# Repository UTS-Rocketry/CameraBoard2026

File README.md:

# CameraBoard – UTS Rocketry Avionics
High-reliability camera control and downlink board built around the **STM32F405RGT6**, designed for UTS Rocketry’s flight avionics stack.  
The board provides **camera power switching**, **camera UART control**, **video downlink support**, and **CAN-based communication** with the central avionics system.

---

## Project Overview
The CameraBoard is a custom PCB designed to interface action cameras with the UTS Rocketry avionics system.  
It provides:

- **Reliable power delivery** to the camera through a load-switch architecture  
- **UART-based camera control** (start/stop recording, mode switching, etc.)  
- **Video downlink support** (placeholder until RF/video module is finalised)  
- **CAN Bus** connectivity for inter-module communication  
- **Debug UART** and activity LEDs  
- **5V → 3.3V power tree** and full onboard decoupling network  

Built around the **STM32F405RGT6**, chosen for performance, CAN support, and strong STM32 ecosystem compatibility.

---

## Key Features
- **STM32F405RGT6 MCU**
- **Camera Power Switching**
  - Load switch controlled via GPIO  
  - Local decoupling + bulk capacitance
- **Camera Control (UART)**
  - Compatible with RunCam-style UART protocols
- **CAN Bus Interface**
  - TX/RX routed to CAN transceiver  
  - Interfaces with the main flight computer
- **Video Downlink Support**
  - Reserved connector footprint  
  - Pins allocated for future video transmitter module
- **Debug Interface**
  - UART for logging  
  - Status, power, and activity LEDs
- **Power Topology**
  - Headers for 5V buck converters  
  - 3.3V rail for MCU and logic  
  - Full decoupling network following ST guidelines

## Current Project Status
Schematic Finalized

## Contributors
Reed Basangan — Software Lead, UTS Rocketry
UTS Rocketry Avionics Team

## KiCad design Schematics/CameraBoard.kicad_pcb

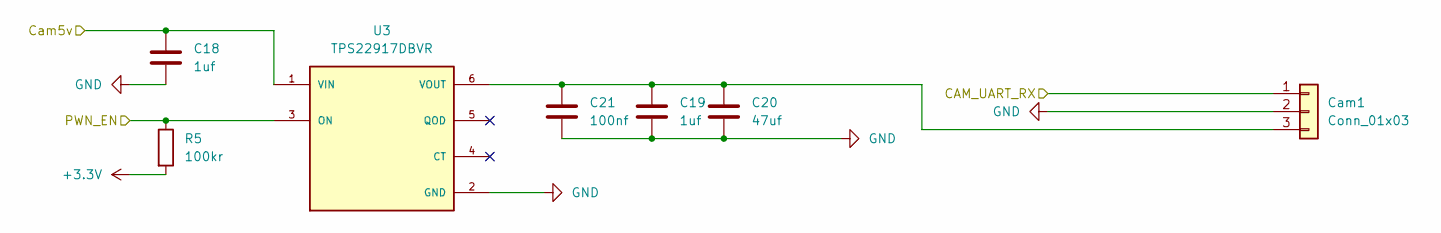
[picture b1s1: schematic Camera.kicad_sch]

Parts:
C18, C19: 1uf; C_0805_2012Metric_Pad1.18x1.45mm_HandSolder; LCSC C28323
C20: 47uf; C_0805_2012Metric_Pad1.18x1.45mm_HandSolder; LCSC C16780
C21: 100nf; C_0805_2012Metric_Pad1.18x1.45mm_HandSolder; LCSC C49678
Cam1: Conn_01x03; JST_PH_B3B-PH-K_1x03_P2.00mm_Vertical; LCSC C131339
R5: 100kr; R_0805_2012Metric_Pad1.20x1.40mm_HandSolder; LCSC C149504
U3: TPS22917DBVR; SOT95P280X145-6N; PARTREV B; LCSC C2681320

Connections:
+3.3V: R5.2; also elsewhere on the board
+5V: C18.1, U3.1 (VIN); also elsewhere on the board
/Camera_center/CAM_UART_RX: Cam1.1; also elsewhere on the board
/Camera_left/<NO NET>: C19.1, C20.1, C21.1, Cam1.3, U3.6 (VOUT)
/Camera_left/PWN_EN: R5.1, U3.3 (ON); also elsewhere on the board
GND: C18.2, C19.2, C20.2, C21.2, Cam1.2, U3.2 (GND); also elsewhere on the board

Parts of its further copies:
C23, C24, C27, C28: 1uf; C_0805_2012Metric_Pad1.18x1.45mm_HandSolder; LCSC C28323
C25, C29: 47uf; C_0805_2012Metric_Pad1.18x1.45mm_HandSolder; LCSC C16780
C26, C30: 100nf; C_0805_2012Metric_Pad1.18x1.45mm_HandSolder; LCSC C49678
Cam2, Cam3: Conn_01x03; JST_PH_B3B-PH-K_1x03_P2.00mm_Vertical; LCSC C131339
R9, R10: 100kr; R_0805_2012Metric_Pad1.20x1.40mm_HandSolder; LCSC C149504
U5, U6: TPS22917DBVR; SOT95P280X145-6N; PARTREV B; LCSC C2681320

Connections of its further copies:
+3.3V: R9.2, R10.2; also elsewhere on the board
+5V: C23.1, C27.1, U5.1 (VIN), U6.1 (VIN); also elsewhere on the board
/Camera_center/<NO NET>: C28.1, C29.1, C30.1, Cam3.3, U6.6 (VOUT)
/Camera_center/CAM_UART_RX: Cam2.1, Cam3.1; also elsewhere on the board
/Camera_center/PWN_EN: R10.1, U6.3 (ON); also elsewhere on the board
/Camera_right/<NO NET>: C24.1, C25.1, C26.1, Cam2.3, U5.6 (VOUT)
/Camera_right/PWN_EN: R9.1, U5.3 (ON); also elsewhere on the board
GND: C23.2, C24.2, C25.2, C26.2, C27.2, C28.2, C29.2, C30.2, Cam2.2, Cam3.2, U5.2 (GND), U6.2 (GND); also elsewhere on the board

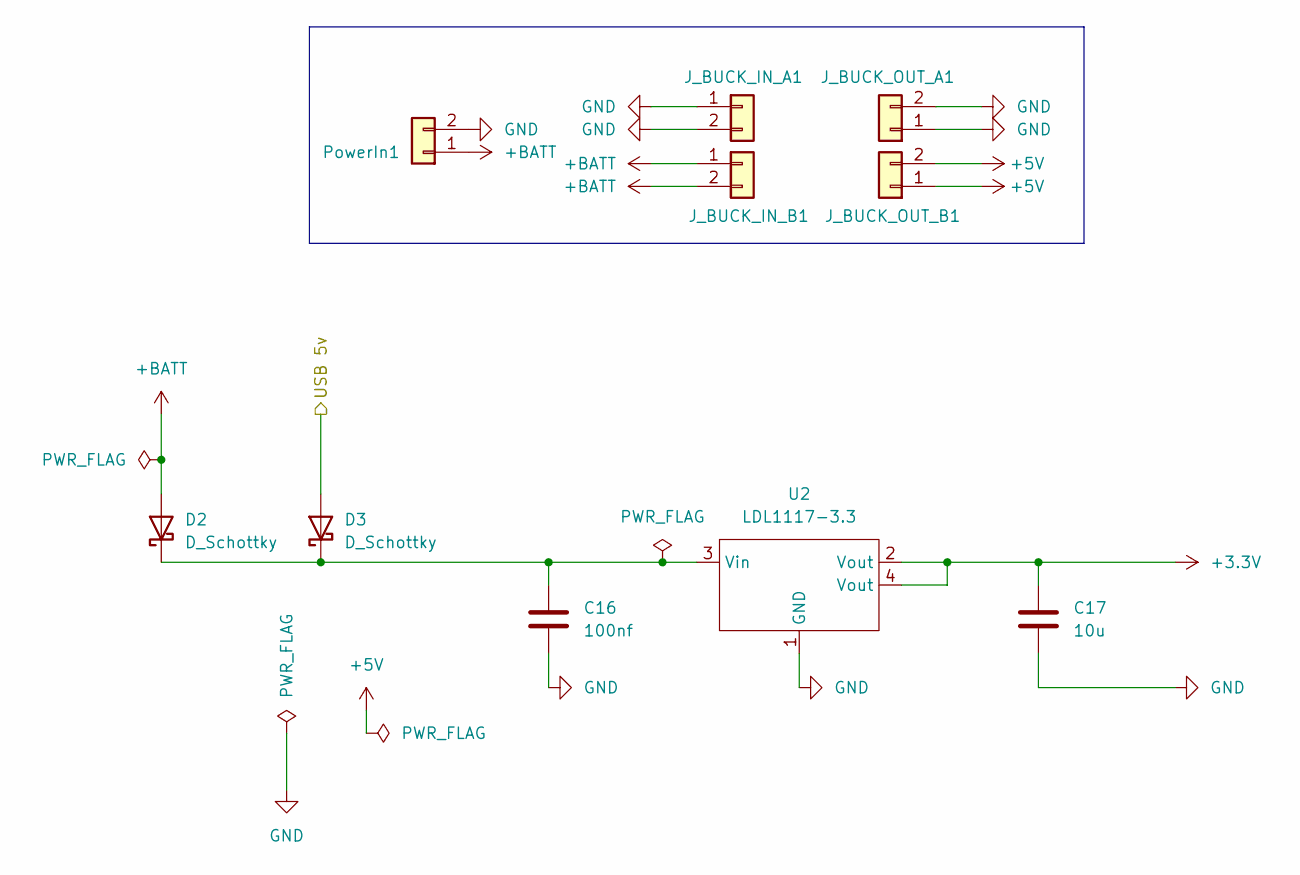
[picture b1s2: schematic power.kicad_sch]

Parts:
C16: 100nf; C_0805_2012Metric_Pad1.18x1.45mm_HandSolder; LCSC Part C28323
C17: 10u; C_0805_2012Metric_Pad1.18x1.45mm_HandSolder; LCSC Part C98192
D2, D3: D_Schottky; D_2114_3652Metric; LCSC C113936
J_BUCK_IN_A1: PinSocket_1x02_P2.54mm_Horizontal
J_BUCK_IN_B1: PinSocket_1x02_P2.54mm_Horizontal
J_BUCK_OUT_A1: PinSocket_1x02_P2.54mm_Horizontal
J_BUCK_OUT_B1: PinSocket_1x02_P2.54mm_Horizontal
PowerIn1: 2 pin Molex; MOLEX_26013114; LCSC C17644051
U2: LDL1117-3.3; SOT230P700X180-4N; LCSC C435835

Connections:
+3.3V: C17.1, U2.2 (Vout), U2.4 (Vout); also elsewhere on the board
+5V: J_BUCK_OUT_B1.1, J_BUCK_OUT_B1.2; also elsewhere on the board
+BATT: D2.2 (A), J_BUCK_IN_B1.1, J_BUCK_IN_B1.2, PowerIn1.1
/MCU/VBUS: D3.2 (A); also elsewhere on the board
GND: C16.2, C17.2, J_BUCK_IN_A1.1, J_BUCK_IN_A1.2, J_BUCK_OUT_A1.1, J_BUCK_OUT_A1.2, PowerIn1.2, U2.1 (GND); also elsewhere on the board
unnamed: C16.1, D2.1 (K), D3.1 (K), U2.3 (Vin)

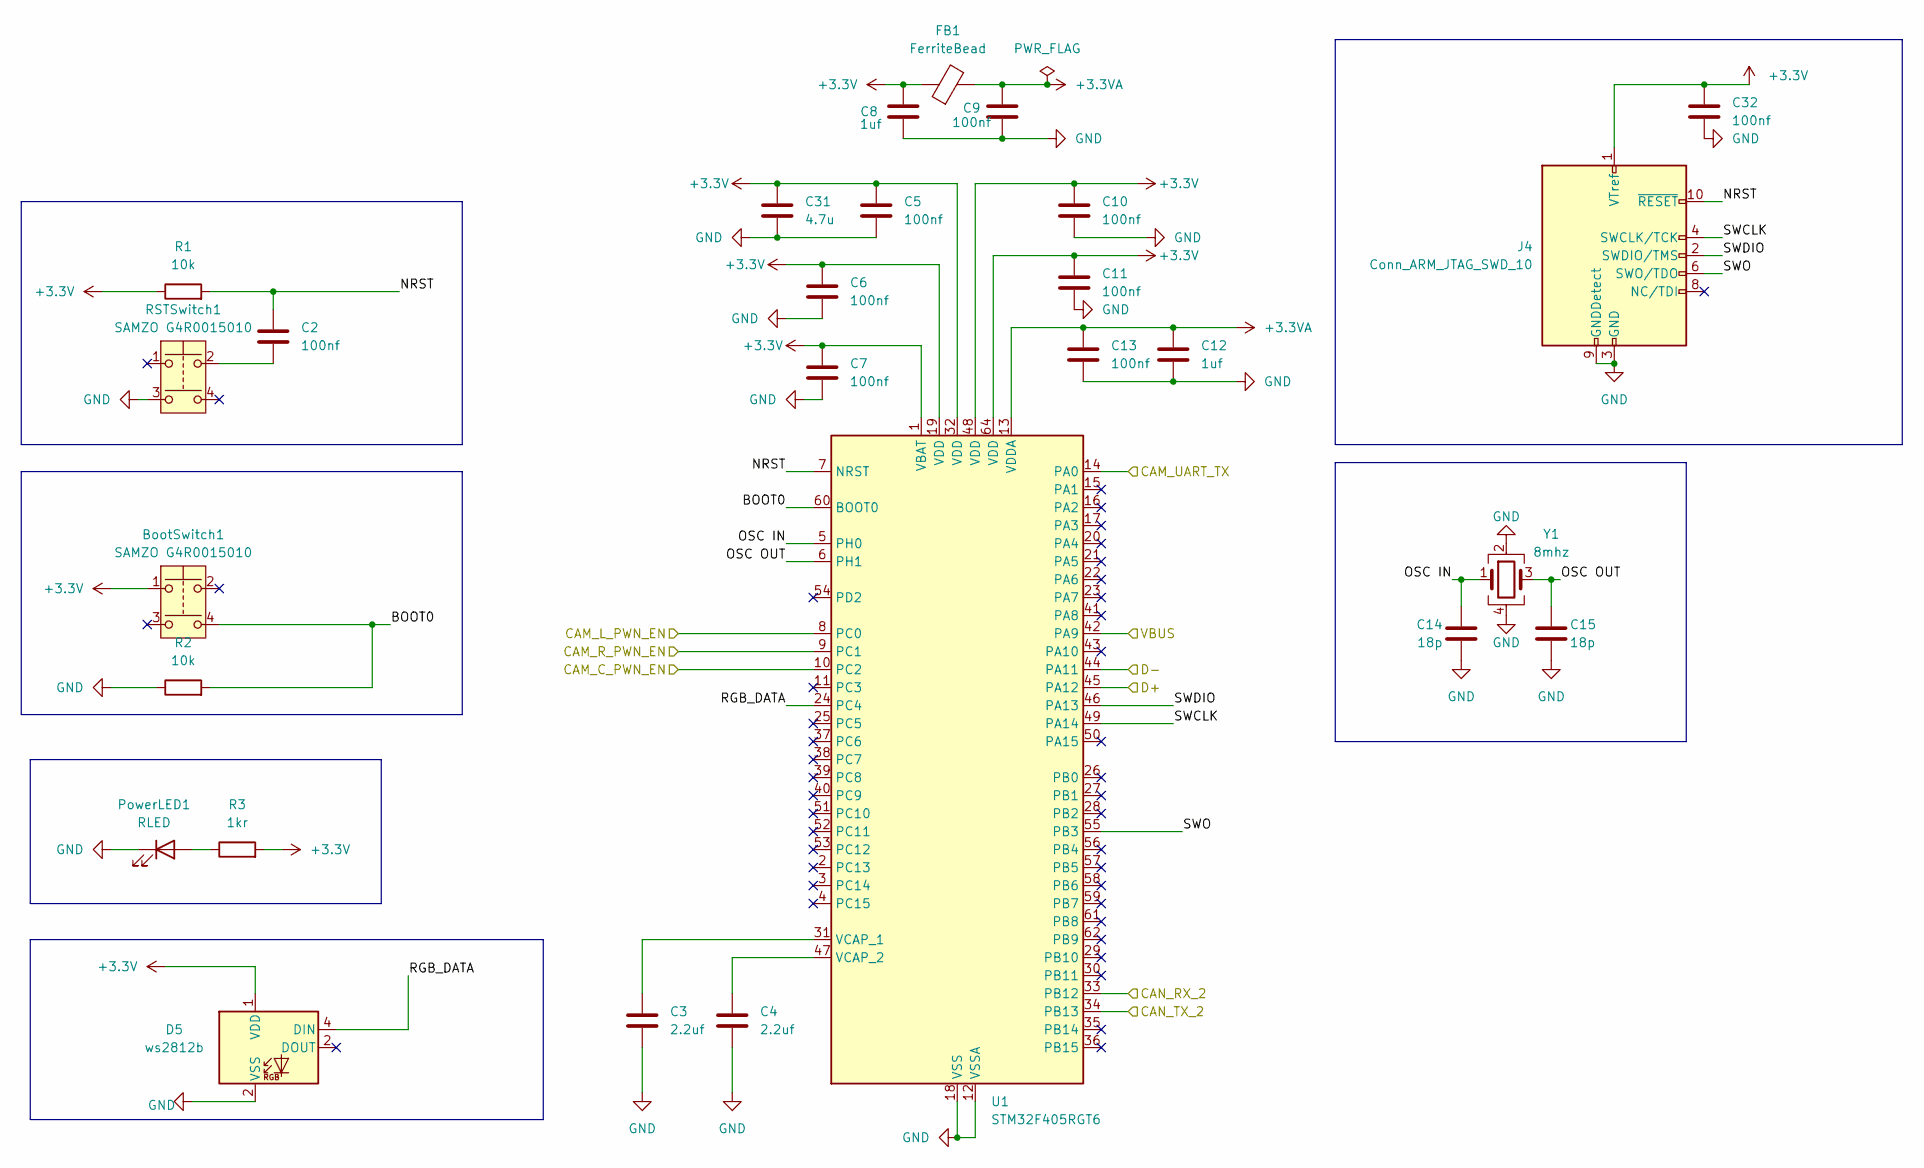
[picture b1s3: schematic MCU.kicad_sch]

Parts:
BootSwitch1: SAMZO G4R0015010; LCSC C49393646
C2, C5, C6, C7, C9, C10, C11, C13, C32: 100nf; C_0805_2012Metric_Pad1.18x1.45mm_HandSolder; LCSC C49678
C3, C4: 2.2uf; C_0805_2012Metric_Pad1.18x1.45mm_HandSolder; LCSC C377773
C8, C12: 1uf; C_0805_2012Metric_Pad1.18x1.45mm_HandSolder; LCSC C28323
C14, C15: 18p; C_0603_1608Metric_Pad1.08x0.95mm_HandSolder; LCSC Part C1647
C31: 4.7u; C_0805_2012Metric_Pad1.18x1.45mm_HandSolder; LCSC C1779
D5: ws2812b; LED_WS2812B_PLCC4_5.0x5.0mm_P3.2mm; LCSC C114586
FB1: FerriteBead; R_0805_2012Metric_Pad1.20x1.40mm_HandSolder; LCSC C85840
J4: Conn_ARM_JTAG_SWD_10; PinHeader_2x05_P1.27mm_Vertical
PowerLED1: RLED; LED_0603_1608Metric_Pad1.05x0.95mm_HandSolder; LCSC C965799
R1, R2: 10k; R_0805_2012Metric_Pad1.20x1.40mm_HandSolder; LCSC C84376
R3: 1kr; R_0805_2012Metric_Pad1.20x1.40mm_HandSolder; LCSC C17513
RSTSwitch1: SAMZO G4R0015010; LCSC C49393646
U1: STM32F405RGT6; LQFP-64_10x10mm_P0.5mm; LCSC C15742
Y1: 8mhz; Crystal_SMD_3225-4Pin_3.2x2.5mm_HandSoldering; LCSC Part C19723344

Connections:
+3.3V: BootSwitch1.1, C5.1, C6.1, C7.1, C8.2, C10.1, C11.1, C31.1, C32.1, D5.1 (VDD), FB1.1, J4.1 (VTref), R1.1, R3.2, U1.1 (VBAT), U1.19 (VDD), U1.32 (VDD), U1.48 (VDD), U1.64 (VDD); also elsewhere on the board
+3.3VA: C9.2, C12.1, C13.1, FB1.2, U1.13 (VDDA)
/Camera_center/CAM_UART_RX: U1.14 (PA0); also elsewhere on the board
/Camera_center/PWN_EN: U1.10 (PC2); also elsewhere on the board
/Camera_left/PWN_EN: U1.8 (PC0); also elsewhere on the board
/Camera_right/PWN_EN: U1.9 (PC1); also elsewhere on the board
/Can_transceiver/CAN_RX_2: U1.33 (PB12); also elsewhere on the board
/Can_transceiver/CAN_TX_2: U1.34 (PB13); also elsewhere on the board
/MCU/BOOT0: BootSwitch1.4, R2.2, U1.60 (BOOT0)
/MCU/D+: U1.45 (PA12); also elsewhere on the board
/MCU/D-: U1.44 (PA11); also elsewhere on the board
/MCU/NRST: C2.1, J4.10 (~RESET), R1.2, U1.7 (NRST)
/MCU/OSC IN: C14.1, U1.5 (PH0), Y1.1
/MCU/OSC OUT: C15.1, U1.6 (PH1), Y1.3
/MCU/RGB_DATA: D5.4 (DIN), U1.24 (PC4)
/MCU/SWCLK: J4.4 (SWCLK/TCK), U1.49 (PA14)
/MCU/SWDIO: J4.2 (SWDIO/TMS), U1.46 (PA13)
/MCU/SWO: J4.6 (SWO/TDO), U1.55 (PB3)
/MCU/VBUS: U1.42 (PA9); also elsewhere on the board
GND: C3.2, C4.2, C5.2, C6.2, C7.2, C8.1, C9.1, C10.2, C11.2, C12.2, C13.2, C14.2, C15.2, C31.2, C32.2, D5.2 (VSS), J4.3 (GND), J4.5 (GND), J4.9 (GNDDetect), PowerLED1.1 (K), R2.1, RSTSwitch1.3, U1.12 (VSSA), U1.18 (VSS), U1.63 (VSS), Y1.2, Y1.4; also elsewhere on the board
unnamed: C2.2, RSTSwitch1.2
unnamed: PowerLED1.2 (A), R3.1
unnamed: C3.1, U1.31 (VCAP_1)
unnamed: C4.1, U1.47 (VCAP_2)

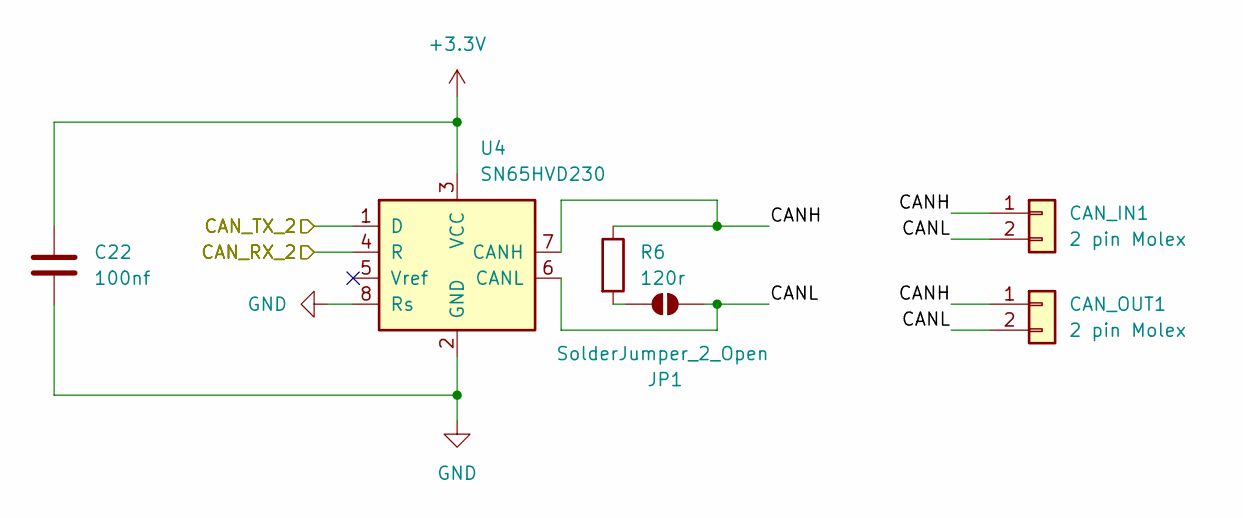
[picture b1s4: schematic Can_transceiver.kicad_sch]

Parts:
C22: 100nf; C_0805_2012Metric_Pad1.18x1.45mm_HandSolder; lcsc C6565120
CAN_IN1: 2 pin Molex; MOLEX_26013114; LCSC C17644051
CAN_OUT1: 2 pin Molex; MOLEX_26013114; LCSC C17644051
JP1: SolderJumper_2_Open; SolderJumper-2_P1.3mm_Open_TrianglePad1.0x1.5mm
R6: 120r; R_0603_1608Metric; lcsc C4353191
U4: SN65HVD230; SOIC-8_3.9x4.9mm_P1.27mm; lcsc C12084

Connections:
+3.3V: C22.1, U4.3 (VCC); also elsewhere on the board
/Can_transceiver/CANH: CAN_IN1.1, CAN_OUT1.1, R6.1, U4.7 (CANH)
/Can_transceiver/CANL: CAN_IN1.2, CAN_OUT1.2, JP1.2 (B), U4.6 (CANL)
/Can_transceiver/CAN_RX_2: U4.4 (R); also elsewhere on the board
/Can_transceiver/CAN_TX_2: U4.1 (D); also elsewhere on the board
GND: C22.2, U4.2 (GND), U4.8 (Rs); also elsewhere on the board
unnamed: JP1.1 (A), R6.2

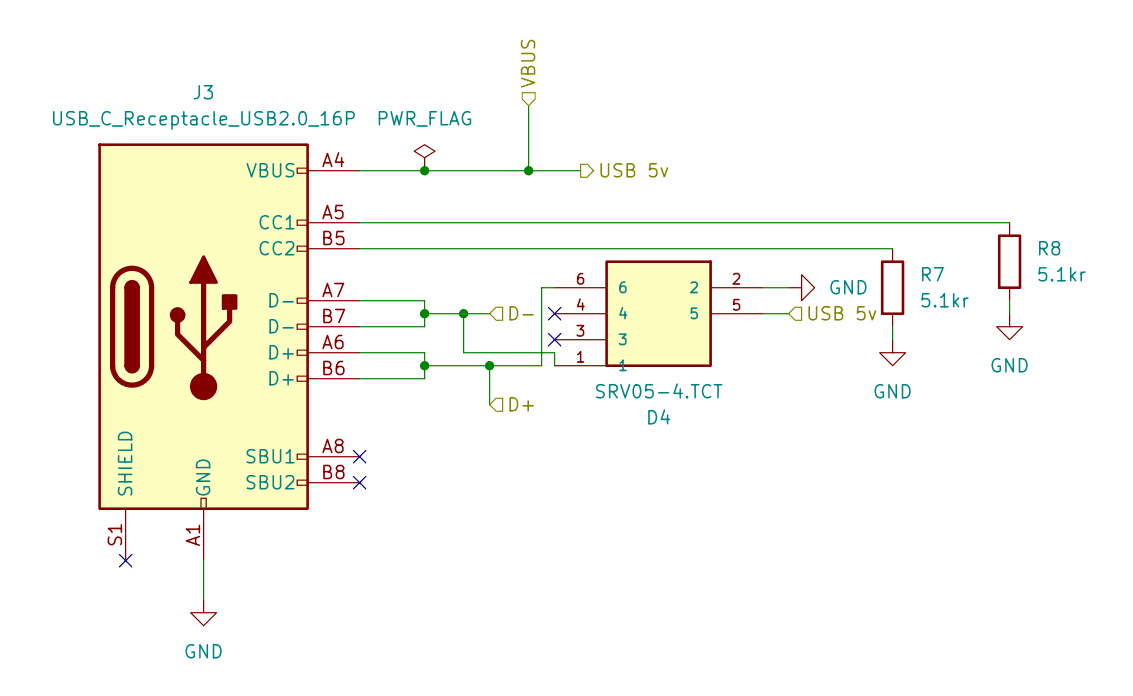
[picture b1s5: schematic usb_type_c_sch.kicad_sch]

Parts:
D4: SRV05-4.TCT; SOT95P280X145-6N; MOUSER_PART_NUMBER 947-SRV05-4.TCT
J3: USB_C_Receptacle_USB2.0_16P; USB_C_Receptacle_HRO_TYPE-C-31-M-12; LCSC C165948
R7, R8: 5.1kr; R_0805_2012Metric_Pad1.20x1.40mm_HandSolder; LCSC C27834

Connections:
/MCU/D+: D4.6, J3.A6 (D+), J3.B6 (D+); also elsewhere on the board
/MCU/D-: D4.1, J3.A7 (D-), J3.B7 (D-); also elsewhere on the board
/MCU/VBUS: D4.5, J3.A4 (VBUS), J3.A9 (VBUS), J3.B4 (VBUS), J3.B9 (VBUS); also elsewhere on the board
GND: D4.2, J3.A1 (GND), J3.A12 (GND), J3.B1 (GND), J3.B12 (GND), R7.2, R8.2; also elsewhere on the board
unnamed: J3.A5 (CC1), R8.1
unnamed: J3.B5 (CC2), R7.1

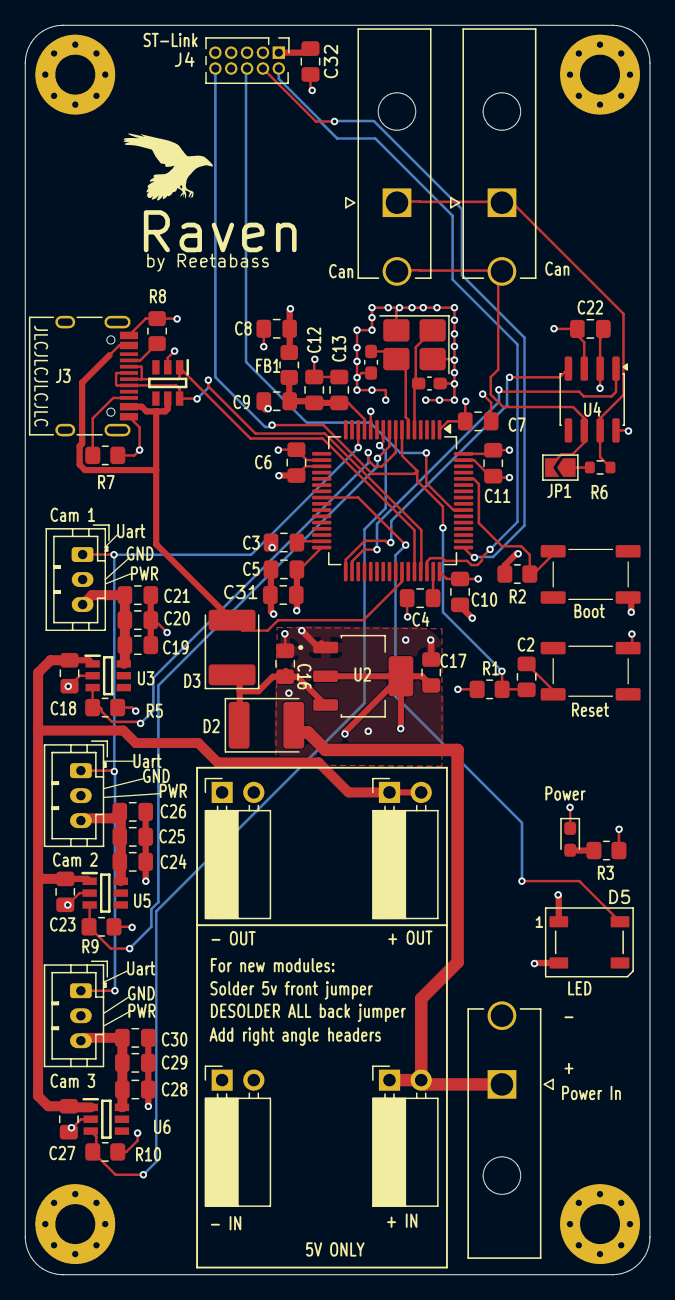
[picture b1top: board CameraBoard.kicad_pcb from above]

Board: 4 copper layers, 50.0 x 100.0 mm, 68 parts (0 on the bottom side), 35 nets.

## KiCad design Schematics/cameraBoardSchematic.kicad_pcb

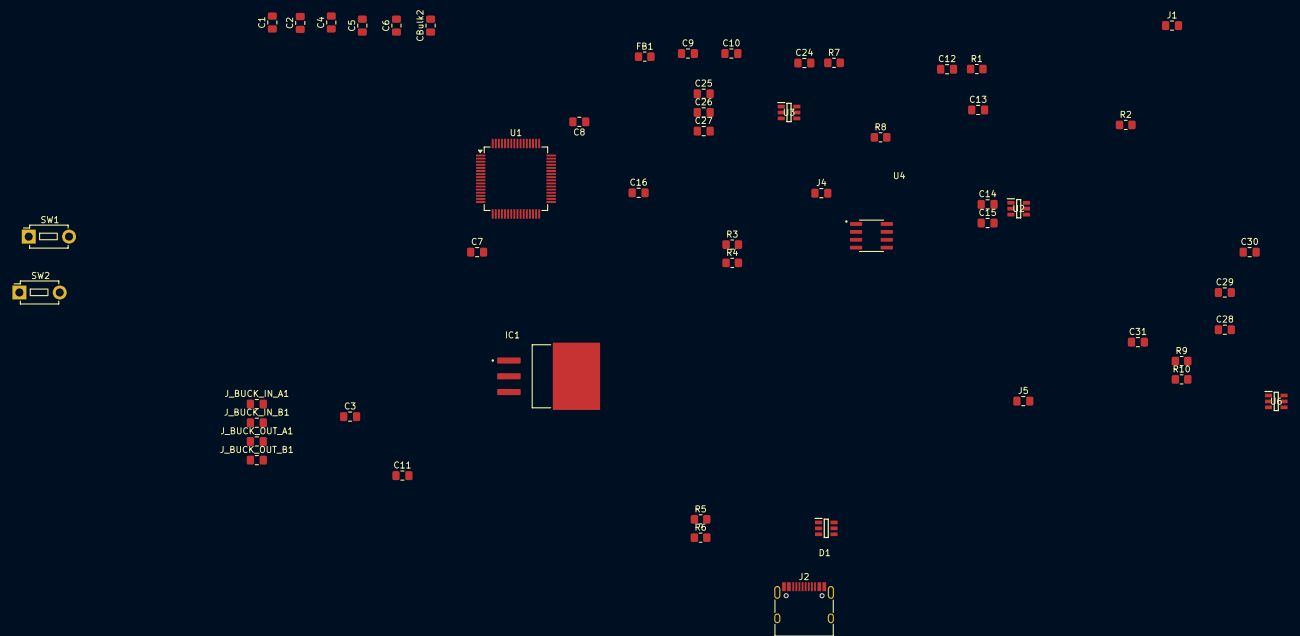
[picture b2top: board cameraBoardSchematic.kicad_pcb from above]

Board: 2 copper layers, 53 parts (0 on the bottom side), 23 nets, no tracks yet.

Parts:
C1, C2, C4, C5, C6, C16: 100nf; C_0805_2012Metric_Pad1.18x1.45mm_HandSolder
C3: .47u; C_0805_2012Metric_Pad1.18x1.45mm_HandSolder
C7, C8: 2.2u; C_0805_2012Metric_Pad1.18x1.45mm_HandSolder
C9, C12, C14, C24, C25, C28, C29: 1u; C_0805_2012Metric_Pad1.18x1.45mm_HandSolder
C10: 10u; C_0805_2012Metric_Pad1.18x1.45mm_HandSolder
C11: 33u; C_0805_2012Metric_Pad1.18x1.45mm_HandSolder
C13, C26, C30: 47u; C_0805_2012Metric_Pad1.18x1.45mm_HandSolder
C15, C27, C31: .1u; C_0805_2012Metric_Pad1.18x1.45mm_HandSolder
CBulk2: 4.7u; C_0805_2012Metric_Pad1.18x1.45mm_HandSolder
D1: SRV05-4.TCT; SOT95P280X145-6N
FB1: FerriteBead; R_0805_2012Metric_Pad1.20x1.40mm_HandSolder
IC1: LM3940IS-3.3_NOPB; TO254P1524X483-4N
J1, J4, J5: Runcam Split 4 v2; C_0805_2012Metric_Pad1.18x1.45mm_HandSolder
J2: USB_C_Receptacle; USB_C_Receptacle_HRO_TYPE-C-31-M-12
J_BUCK_IN_A1: C_0805_2012Metric_Pad1.18x1.45mm_HandSolder
J_BUCK_IN_B1: C_0805_2012Metric_Pad1.18x1.45mm_HandSolder
J_BUCK_OUT_A1: C_0805_2012Metric_Pad1.18x1.45mm_HandSolder
J_BUCK_OUT_B1: C_0805_2012Metric_Pad1.18x1.45mm_HandSolder
R1: 22k; R_0805_2012Metric_Pad1.20x1.40mm_HandSolder
R2, R3, R7, R9: 100k; R_0805_2012Metric_Pad1.20x1.40mm_HandSolder
R4: 10k; R_0805_2012Metric_Pad1.20x1.40mm_HandSolder
R5, R6: 5.1k; R_0805_2012Metric_Pad1.20x1.40mm_HandSolder
R8, R10: 1k; R_0805_2012Metric_Pad1.20x1.40mm_HandSolder
SW1, SW2: SW_Push; SW_PUSH_1P1T_6x3.5mm_H5.0_APEM_MJTP1250
U1: STM32F405RGTx; LQFP-64_10x10mm_P0.5mm
U2, U3, U6: TPS22917DBVR; SOT95P280X145-6N
U4: SN65HVD230DR; SOIC127P599X175-8N

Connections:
+3.3V: C1.1, C2.1, C4.1, C5.1, C6.1, C11.1, CBulk2.1, FB1.1, IC1.3 (VOUT), R2.2, R4.1, R7.2, R9.2, SW1.1, U1.1 (VBAT), U1.13 (VDDA), U1.19 (VDD), U1.32 (VDD), U1.48 (VDD), U1.64 (VDD)
+3.3VA: C9.2, C10.2, FB1.2
+5V: C3.1, C12.1, C24.1, C28.1, D1.5, IC1.1 (VIN), J2.A4 (VBUS), J2.A9 (VBUS), J2.B4 (VBUS), J2.B9 (VBUS), J_BUCK_OUT_A1.1, J_BUCK_OUT_B1.1, U2.1 (VIN), U3.1 (VIN), U6.1 (VIN)
/Camera_center/<NO NET>: C29.1, C30.1, C31.1, U6.5 (QOD), U6.6 (VOUT)
/Camera_center/CAM_C_PWN_EN: R9.1, U6.3 (ON)
/Camera_center/CAM_UART_TX: J5.1 (RX), R10.1
/Camera_left/<NO NET>: C13.1, C14.1, C15.1, U2.5 (QOD), U2.6 (VOUT)
/Camera_left/CAM_L_PWN_EN: R2.1, U2.3 (ON)
/Camera_left/CAM_UART_TX: J1.1 (RX), R1.1
/Camera_right/<NO NET>: C25.1, C26.1, C27.1, U3.5 (QOD), U3.6 (VOUT)
/Camera_right/CAM_R_PWN_EN: R7.1, U3.3 (ON)
/Camera_right/CAM_UART_TX: J4.1 (RX), R8.1
/MCU/BOOT0: R3.2, SW1.2, U1.60 (BOOT0)
/MCU/NRST: C16.1, R4.2, U1.7 (NRST)
/Power/VBAT: J_BUCK_IN_A1.1, J_BUCK_IN_B1.1
/usb_type_c/D+: D1.1, J2.A6 (D+), J2.B6 (D+)
/usb_type_c/D-: D1.3, J2.A7 (D-), J2.B7 (D-)
GND: C1.2, C2.2, C3.2, C4.2, C5.2, C6.2, C7.2, C8.2, C9.1, C10.1, C11.2, C12.2, C13.2, C14.2, C15.2, C24.2, C25.2, C26.2, C27.2, C28.2, C29.2, C30.2, C31.2, CBulk2.2, D1.2, IC1.2 (GND), J2.A1 (GND), J2.A12 (GND), J2.B1 (GND), J2.B12 (GND), J2.S1 (SHIELD), J_BUCK_IN_A1.2, J_BUCK_IN_B1.2, J_BUCK_OUT_A1.2, R1.2, R3.1, R5.2, R6.2, R8.2, R10.2, SW2.1, U1.12 (VSSA), U1.18 (VSS), U1.63 (VSS), U2.2 (GND), U3.2 (GND), U4.2 (GND), U4.8 (RS), U6.2 (GND)
unnamed: C16.2, SW2.2
unnamed: J2.A5 (CC1), R5.1
unnamed: J2.B5 (CC2), R6.1
unnamed: C7.1, U1.31 (VCAP_1)
unnamed: C8.1, U1.47 (VCAP_2)

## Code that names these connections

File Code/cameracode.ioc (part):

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Mcu.Name=STM32F405RGTx
Mcu.Package=LQFP64
Mcu.UserName=STM32F405RGTx
PA0-WKUP.GPIOParameters=GPIO_Label
PA0-WKUP.GPIO_Label=cameratx
PA0-WKUP.Signal=UART4_TX
PA11.Mode=Device_Only
PA11.Signal=USB_OTG_FS_DM
PA12.Mode=Device_Only
PA12.Signal=USB_OTG_FS_DP
PA13.Mode=Serial_Wire
PA13.Signal=SYS_JTMS-SWDIO
PA14.Mode=Serial_Wire
PA14.Signal=SYS_JTCK-SWCLK
PB12.Mode=CAN_Activate
PB12.Signal=CAN2_RX
PB13.Mode=CAN_Activate
PB13.Signal=CAN2_TX
PC0.GPIOParameters=GPIO_Label
PC0.GPIO_Label=CAM_L_PWN_EN
PC0.Signal=GPIO_Output
PC1.GPIOParameters=GPIO_Label
PC1.GPIO_Label=CAM_R_PWN_EN
PC1.Signal=GPIO_Output
PC2.GPIOParameters=GPIO_Label
PC2.GPIO_Label=CAM_C_PWN_EN
PC2.Signal=GPIO_Output
PC4.GPIOParameters=GPIO_Label
PC4.GPIO_Label=RGB_led
PC4.Signal=GPIO_Output
PH0-OSC_IN.Mode=HSE-External-Oscillator
PH0-OSC_IN.Signal=RCC_OSC_IN
PH1-OSC_OUT.Mode=HSE-External-Oscillator
PH1-OSC_OUT.Signal=RCC_OSC_OUT
RCC.HSE_VALUE=8000000
RCC.SYSCLKFreq_VALUE=72000000
RCC.SYSCLKSource=RCC_SYSCLKSOURCE_PLLCLK
board=custom

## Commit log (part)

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2025-12-01 Add initial README for CameraBoard project
2025-12-08 added usb type C and changed to CAN2
2025-12-10 finished LED one Power and one Programable
2026-01-06 assigned footprints ready for pcb design
2026-01-08 Fixed footprint assignments pcb dev begining
2026-01-14 first PCB Draft
2026-01-17 fixing merge
2026-01-17 fixing duplicate project files and fixing github merge conflict
2026-01-19 Replaced LDO with smaller & Fixed resistor value for Camera tx lines
2026-01-20 added pin headers for connectors and added buck connector connections, rounding done and mounting holes included, routing will occur after review
2026-01-20 fixed spacing issues
2026-01-21 began routing
2026-01-22 fixing routing redefining layout
2026-01-27 finalizing layout and saving space add all correct connectors and components
2026-01-29 replaced items under buck module almost ready for routing
2026-01-29 Fixed Schematic and PCB refrences everything is connected correctly now
2026-02-02 fixed all refrences from shematic to pcb and added LED
2026-02-02 all nets are correct within PCB and correct CAN is implemented
2026-02-03 fixed silkscreen
2026-02-04 routing taking place only USB to do
2026-02-04 added graphics
2026-02-04 routing done pending final review
2026-02-04 fixed can routing
2026-02-06 Cleaned up schematic added ocilator added jtag 10 pin begining routing again
2026-02-06 routing taking place all layout is complete fixed all text
2026-02-06 second final draft finished routing added swd debug with stlink capabilities pending review for and data sheet review to ensure parts are correct, also need to edge cut ocillator
2026-02-07 after review: Changed orientation of molex connectors moved sensitive datalines away from the buck converter, have to reroute but layout is pending and will route when approved, fixed sizeing Standar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
2026-02-09 final draft pending final review
2026-02-09 added LCSC numbers and generated BOM, fixed schematic
2026-02-09 Fixed duplicate sheets
2026-02-10 fixed switch layout and unrouted nets
2026-02-10 Ran ERC added Pwr Flags
2026-02-10 Ran DRC: no errors
2026-02-10 ran DRC, passed awaiting final review
2026-02-16 final design pcb
2026-02-17 added rules area for ocilator and copper area for ldo
2026-02-17 fixed ocilator route lengths
2026-02-17 fixed rule area and cap
2026-05-25 init - code initialisation
2026-05-26 appdrivers are done - need to review: the led status is blink pattern driver, camera control is TX only UART camera command driver. the camera power controls the cam L/P/C and the CAn init, filter co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
2026-05-26 recording toggle fix. and TX only
2026-05-26 defining the start and stop, to configure later to send signals
2026-05-28 camera uart works.
2026-05-28 camera board commands working.
2026-06-03 ready for initial record and save tests, updated the logic to stop auto record after boot and then start auto recording after 5 min and then stop again after 20 sec
